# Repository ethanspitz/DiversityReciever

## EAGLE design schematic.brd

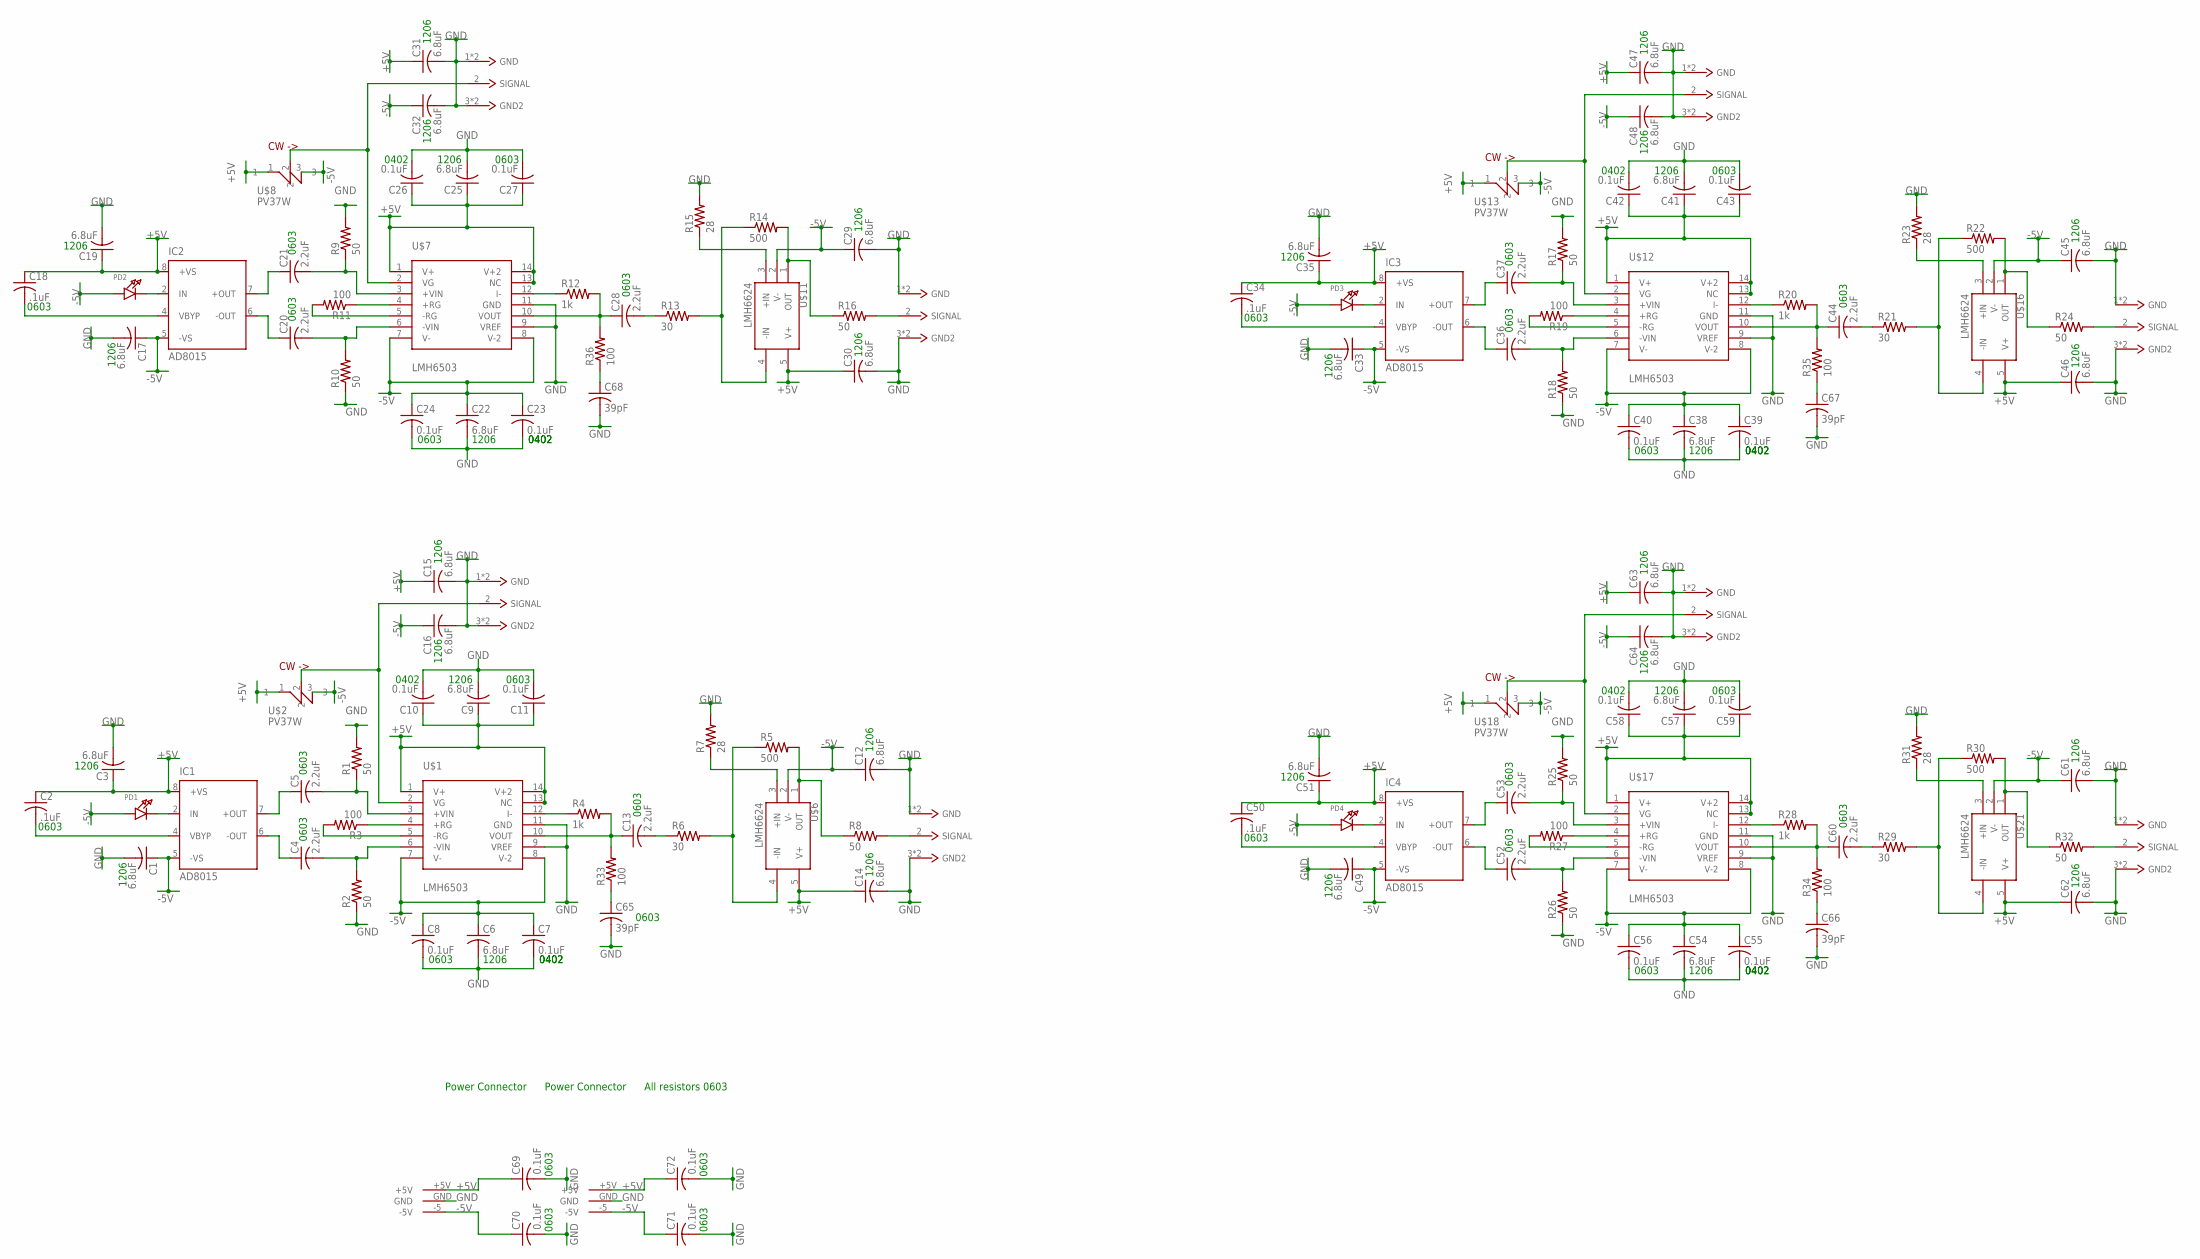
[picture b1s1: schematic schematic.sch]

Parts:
C1, C3, C6, C9, C12, C14, C15, C16, C17, C19, C22, C25, C29, C30, C31, C32, C33, C35, C38, C41, C45, C46, C47, C48, C49, C51, C54, C57, C61, C62, C63, C64: 6.8uF; C1206
C2, C18, C34, C50: .1uF; C0603
C4, C5, C13, C20, C21, C28, C36, C37, C44, C52, C53, C60: 2.2uF; C0603
C7, C10, C23, C26, C39, C42, C55, C58, C69, C70, C71, C72: 0.1uF; C0402
C8, C11, C24, C27, C40, C43, C56, C59: 0.1uF; C0603
C65, C66, C67, C68: 39pF; C0603
IC1, IC2, IC3, IC4: AD8015; SO8
PD1, PD2, PD3, PD4: LED1206; CHIPLED_1206
R1, R2, R8, R9, R10, R16, R17, R18, R24, R25, R26, R32: 50; R0603
R3, R11, R19, R27, R33, R34, R35, R36: 100; R0603
R4, R12, R20, R28: 1k; R0603
R5, R14, R22, R30: 500; R0603
R6, R13, R21, R29: 30; R0603
R7, R15, R23, R31: 28; R0603
U$1, U$7, U$12, U$17: LMH6503; SOIC14
U$2, U$8, U$13, U$18: PV37W
U$3, U$22: DIVERSITYPWR; DIVERSITYPOWER
U$4, U$5, U$9, U$10, U$14, U$15, U$19, U$20: BNCCONN; BNCPADS
U$6, U$11, U$16, U$21: LMH6624; SOT-23

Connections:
+5V: C2.1, C3.1, C9.1, C10.1, C11.1, C14.1, C15.1, C18.1, C19.1, C25.1, C26.1, C27.1, C30.1, C31.1, C34.1, C35.1, C41.1, C42.1, C43.1, C46.1, C47.1, C50.1, C51.1, C57.1, C58.1, C59.1, C62.1, C63.1, C69.1, C72.1, IC1.8 (+VS), IC2.8 (+VS), IC3.8 (+VS), IC4.8 (+VS), U$1.1 (V+), U$1.13 (NC), U$1.14 (V+2), U$2.1, U$3.+5V, U$6.5 (V+), U$7.1 (V+), U$7.13 (NC), U$7.14 (V+2), U$8.1, U$11.5 (V+), U$12.1 (V+), U$12.13 (NC), U$12.14 (V+2), U$13.1, U$16.5 (V+), U$17.1 (V+), U$17.13 (NC), U$17.14 (V+2), U$18.1, U$21.5 (V+), U$22.+5V
-5V: C1.1, C6.1, C7.1, C8.1, C12.1, C16.1, C17.1, C22.1, C23.1, C24.1, C29.1, C32.1, C33.1, C38.1, C39.1, C40.1, C45.1, C48.1, C49.1, C54.1, C55.1, C56.1, C61.1, C64.1, C70.1, C71.1, IC1.5 (-VS), IC2.5 (-VS), IC3.5 (-VS), IC4.5 (-VS), PD1.A, PD2.A, PD3.A, PD4.A, U$1.7 (V-), U$1.8 (V-2), U$2.3, U$3.-5 (-5V), U$6.2 (V-), U$7.7 (V-), U$7.8 (V-2), U$8.3, U$11.2 (V-), U$12.7 (V-), U$12.8 (V-2), U$13.3, U$16.2 (V-), U$17.7 (V-), U$17.8 (V-2), U$18.3, U$21.2 (V-), U$22.-5 (-5V)
GND: C1.2, C3.2, C6.2, C7.2, C8.2, C9.2, C10.2, C11.2, C12.2, C14.2, C15.2, C16.2, C17.2, C19.2, C22.2, C23.2, C24.2, C25.2, C26.2, C27.2, C29.2, C30.2, C31.2, C32.2, C33.2, C35.2, C38.2, C39.2, C40.2, C41.2, C42.2, C43.2, C45.2, C46.2, C47.2, C48.2, C49.2, C51.2, C54.2, C55.2, C56.2, C57.2, C58.2, C59.2, C61.2, C62.2, C63.2, C64.2, C65.2, C66.2, C67.2, C68.2, C69.2, C70.2, C71.2, C72.2, R1.2, R2.1, R7.2, R9.2, R10.1, R15.2, R17.2, R18.1, R23.2, R25.2, R26.1, R31.2, U$1.9 (VREF), U$1.11 (GND), U$3.GND, U$4.1 (GND), U$4.3 (GND2), U$4.4 (GND), U$4.5 (GND2), U$5.1 (GND), U$5.3 (GND2), U$5.4 (GND), U$5.5 (GND2), U$7.9 (VREF), U$7.11 (GND), U$9.1 (GND), U$9.3 (GND2), U$9.4 (GND), U$9.5 (GND2), U$10.1 (GND), U$10.3 (GND2), U$10.4 (GND), U$10.5 (GND2), U$12.9 (VREF), U$12.11 (GND), U$14.1 (GND), U$14.3 (GND2), U$14.4 (GND), U$14.5 (GND2), U$15.1 (GND), U$15.3 (GND2), U$15.4 (GND), U$15.5 (GND2), U$17.9 (VREF), U$17.11 (GND), U$19.1 (GND), U$19.3 (GND2), U$19.4 (GND), U$19.5 (GND2), U$20.1 (GND), U$20.3 (GND2), U$20.4 (GND), U$20.5 (GND2), U$22.GND
unnamed: IC1.2 (IN), PD1.C
unnamed: C5.1, IC1.7 (+OUT)
unnamed: C2.2, IC1.4 (VBYP)
unnamed: C4.1, IC1.6 (-OUT)
unnamed: C4.2, R2.2, U$1.6 (-VIN)
unnamed: C5.2, R1.1, U$1.3 (+VIN)
unnamed: R3.1, U$1.4 (+RG)
unnamed: R3.2, U$1.5 (-RG)
unnamed: R4.1, U$1.12 (I-)
unnamed: C13.1, R4.2, R33.2, U$1.10 (VOUT)
unnamed: R5.1, R6.2, U$6.4 (-IN)
unnamed: C13.2, R6.1
unnamed: U$1.2 (VG), U$2.2, U$4.2 (SIGNAL)
unnamed: R8.2, U$5.2 (SIGNAL)
unnamed: R7.1, U$6.3 (+IN)
unnamed: R5.2, R8.1, U$6.1 (OUT)
unnamed: C18.2, IC2.4 (VBYP)
unnamed: IC2.2 (IN), PD2.C
unnamed: C21.1, IC2.7 (+OUT)
unnamed: C20.1, IC2.6 (-OUT)
unnamed: C20.2, R10.2, U$7.6 (-VIN)
unnamed: C21.2, R9.1, U$7.3 (+VIN)
unnamed: R11.1, U$7.4 (+RG)
unnamed: R11.2, U$7.5 (-RG)
unnamed: R12.1, U$7.12 (I-)
unnamed: C28.1, R12.2, R36.2, U$7.10 (VOUT)
unnamed: C28.2, R13.1
unnamed: U$7.2 (VG), U$8.2, U$9.2 (SIGNAL)
unnamed: R13.2, R14.1, U$11.4 (-IN)
unnamed: R15.1, U$11.3 (+IN)
unnamed: R14.2, R16.1, U$11.1 (OUT)
unnamed: R16.2, U$10.2 (SIGNAL)
unnamed: C34.2, IC3.4 (VBYP)
unnamed: IC3.2 (IN), PD3.C
unnamed: C37.1, IC3.7 (+OUT)
unnamed: C36.1, IC3.6 (-OUT)
unnamed: C36.2, R18.2, U$12.6 (-VIN)
unnamed: C37.2, R17.1, U$12.3 (+VIN)
unnamed: R19.1, U$12.4 (+RG)
unnamed: R19.2, U$12.5 (-RG)
unnamed: R20.1, U$12.12 (I-)
unnamed: C44.1, R20.2, R35.2, U$12.10 (VOUT)
unnamed: C44.2, R21.1
unnamed: U$12.2 (VG), U$13.2, U$14.2 (SIGNAL)
unnamed: R21.2, R22.1, U$16.4 (-IN)
unnamed: R23.1, U$16.3 (+IN)
unnamed: R22.2, R24.1, U$16.1 (OUT)
unnamed: R24.2, U$15.2 (SIGNAL)
unnamed: C50.2, IC4.4 (VBYP)
unnamed: IC4.2 (IN), PD4.C
unnamed: C53.1, IC4.7 (+OUT)
unnamed: C52.1, IC4.6 (-OUT)
unnamed: C52.2, R26.2, U$17.6 (-VIN)
unnamed: C53.2, R25.1, U$17.3 (+VIN)
unnamed: R27.1, U$17.4 (+RG)
unnamed: R27.2, U$17.5 (-RG)
unnamed: R28.1, U$17.12 (I-)
unnamed: C60.1, R28.2, R34.2, U$17.10 (VOUT)
unnamed: C60.2, R29.1
unnamed: U$17.2 (VG), U$18.2, U$19.2 (SIGNAL)
unnamed: R29.2, R30.1, U$21.4 (-IN)
unnamed: R31.1, U$21.3 (+IN)
unnamed: R30.2, R32.1, U$21.1 (OUT)
unnamed: R32.2, U$20.2 (SIGNAL)
unnamed: C65.1, R33.1
unnamed: C66.1, R34.1
unnamed: C67.1, R35.1
unnamed: C68.1, R36.1

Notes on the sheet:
Power Connector
0402
0603
1206
All resistors 0603

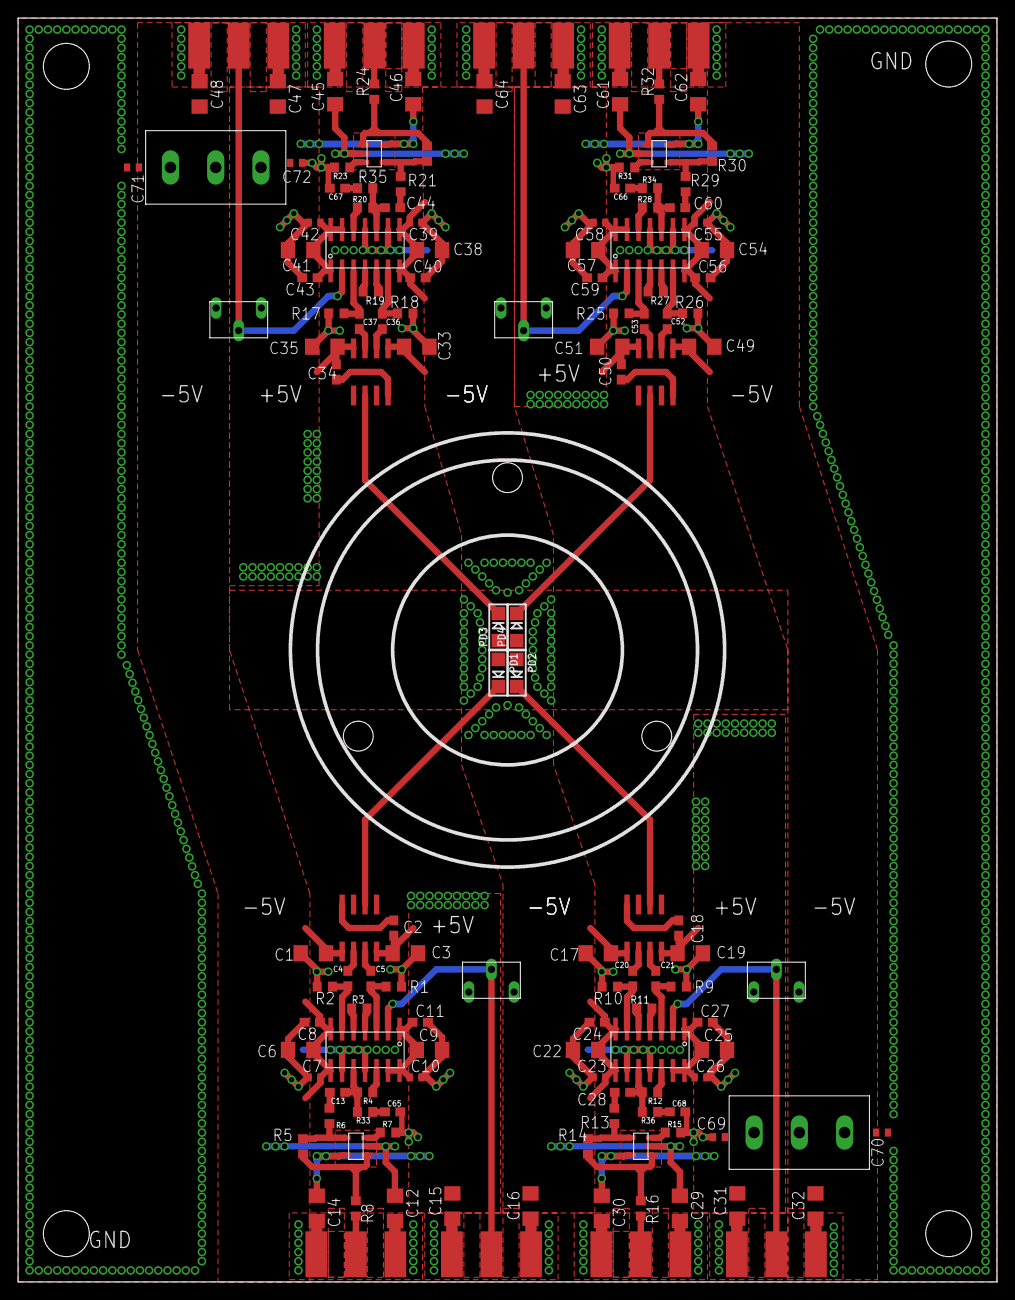
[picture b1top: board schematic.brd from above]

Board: 2 copper layers, 108.2 x 139.7 mm, 138 parts (0 on the bottom side), 71 nets.

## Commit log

2013-04-06 Finished main schematic
    Still to layout and copy three times
2013-04-06 Finished initial layout
2013-04-06 Fixed DRC Error and second circuit
2013-04-06 Added rest of copies and wired everything together.
    Need to add silkscreen and fix photo diodes
2013-04-07 Reorganized board to reduce parasitic factors.
2013-04-08 Added LMH6624 to end. Major layout rework for high freq AC .
    Still has problems. LMH6624 has power inputs on the wrong side of the
    chip making it hard to wire to power plane. GND plane is heavily split
    in the process of connecting power planes.
2013-04-09 Updated LMH6624 Layout to be able to reach power with minimal capacitance on the feedback loop
2013-04-09 Removed some congestion by the LMH6624
2013-04-11 Added second channel
2013-04-11 Added third channel
2013-04-11 Added fourth channel and lined up
2013-04-11 Added second power plug
2013-04-11 Initial Silkscreen and photodiode layout with some initial power plane connections
    needs fixing, some unresolved problems
2013-04-11 Realigned top and bottom to optimize photodiode trace length
2013-04-11 Silkscreen updated for each channel fixed vias by connectors
2013-04-13 Connected more power planes
2013-04-13 Wired all power planes, need to fine "unrouted" connections
2013-04-13 Fixed unrouted, added top gnd plane
2013-04-15 Added Holes
2013-04-16 Doubled up all vias
2013-04-16 Added snubber network to each circuit in schematic and layout
2013-04-16 Minor silk screen changes
2013-04-17 Added more vias around the top ground plane
2013-04-17 Added holes in the corners for mounting
2013-04-17 Added bypass caps
2013-04-19 Fixed BNC package and updated schematic labels

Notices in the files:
parts and their libraries:
microbuilder: This work is placed in the public domain, and may be freely used for commercial and non-commercial work with the following conditions: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
